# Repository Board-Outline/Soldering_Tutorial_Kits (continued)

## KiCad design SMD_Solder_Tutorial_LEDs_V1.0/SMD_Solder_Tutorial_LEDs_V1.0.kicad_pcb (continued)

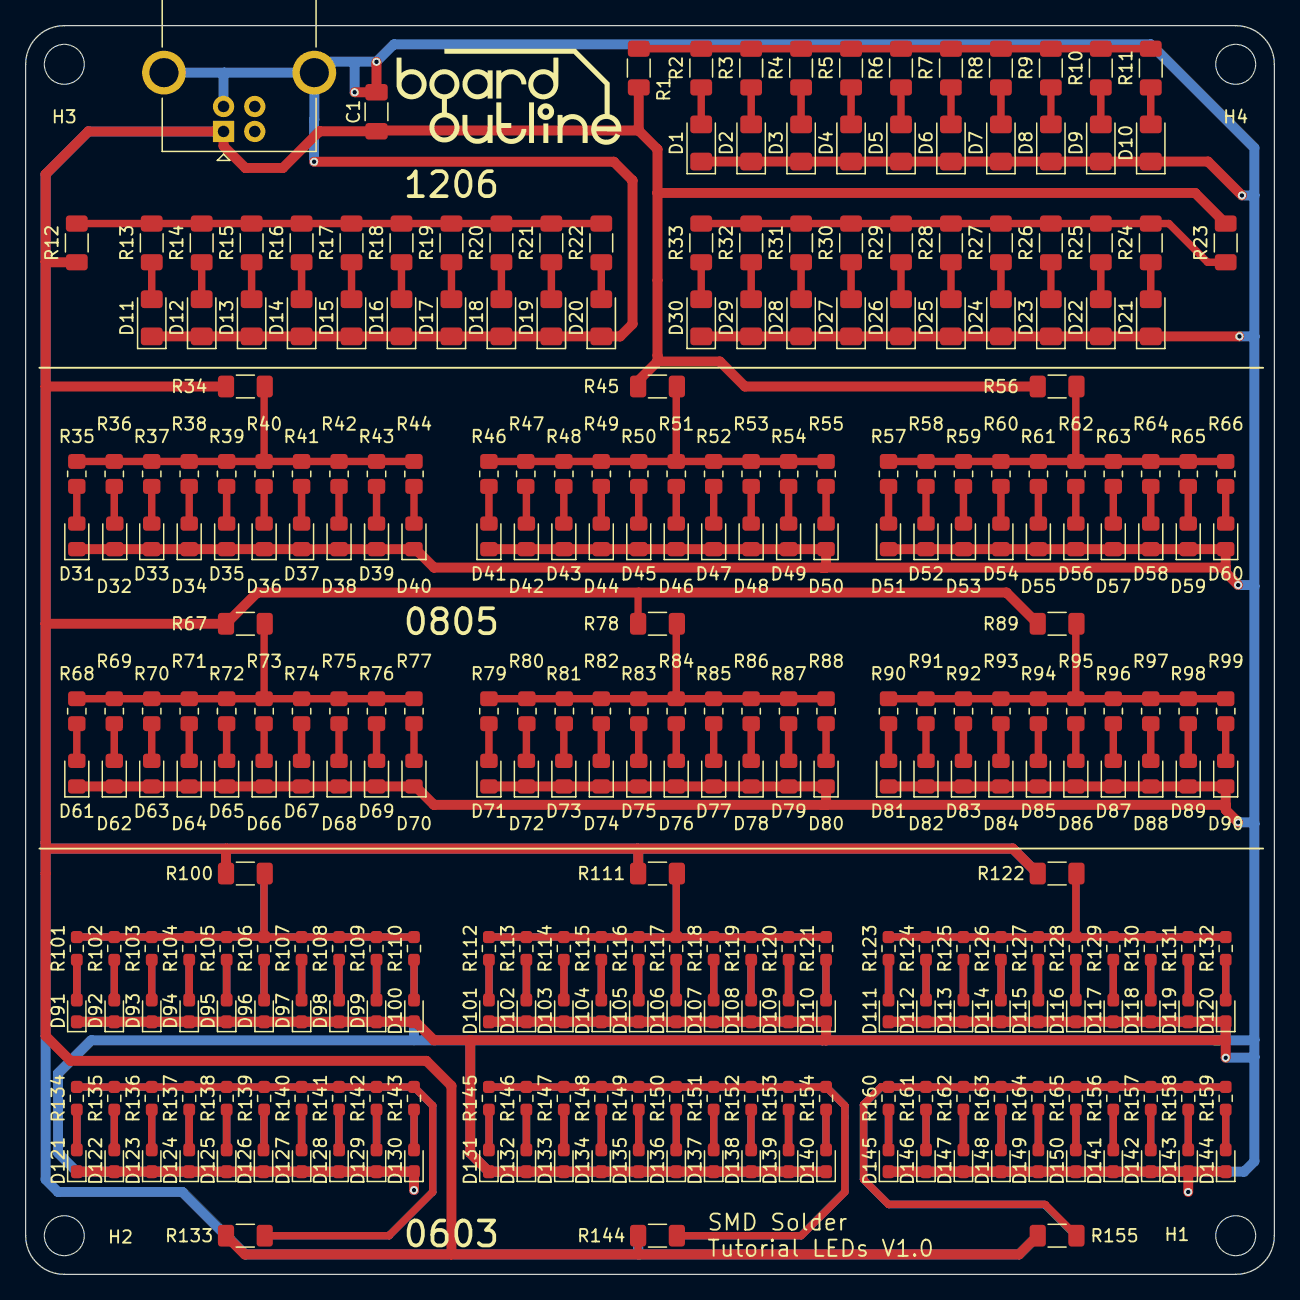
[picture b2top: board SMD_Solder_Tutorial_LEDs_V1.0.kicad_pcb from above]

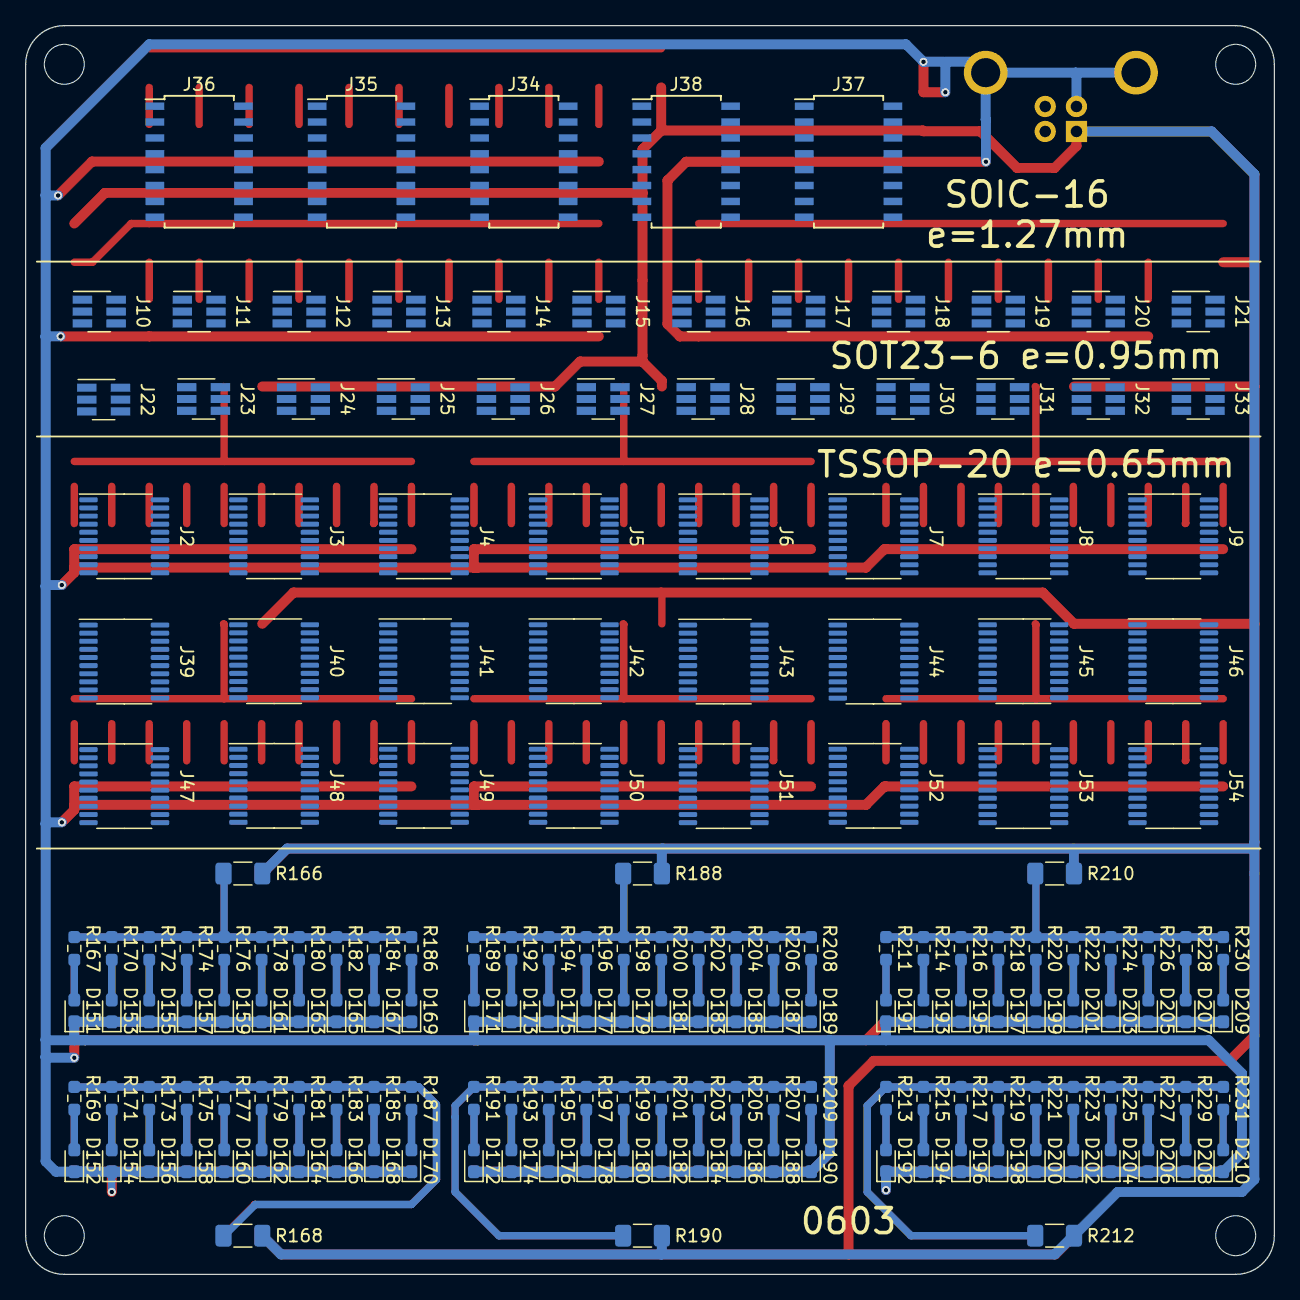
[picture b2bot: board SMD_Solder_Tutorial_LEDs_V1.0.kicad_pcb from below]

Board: 2 copper layers, 100.0 x 100.0 mm, 500 parts (179 on the bottom side), 233 nets.

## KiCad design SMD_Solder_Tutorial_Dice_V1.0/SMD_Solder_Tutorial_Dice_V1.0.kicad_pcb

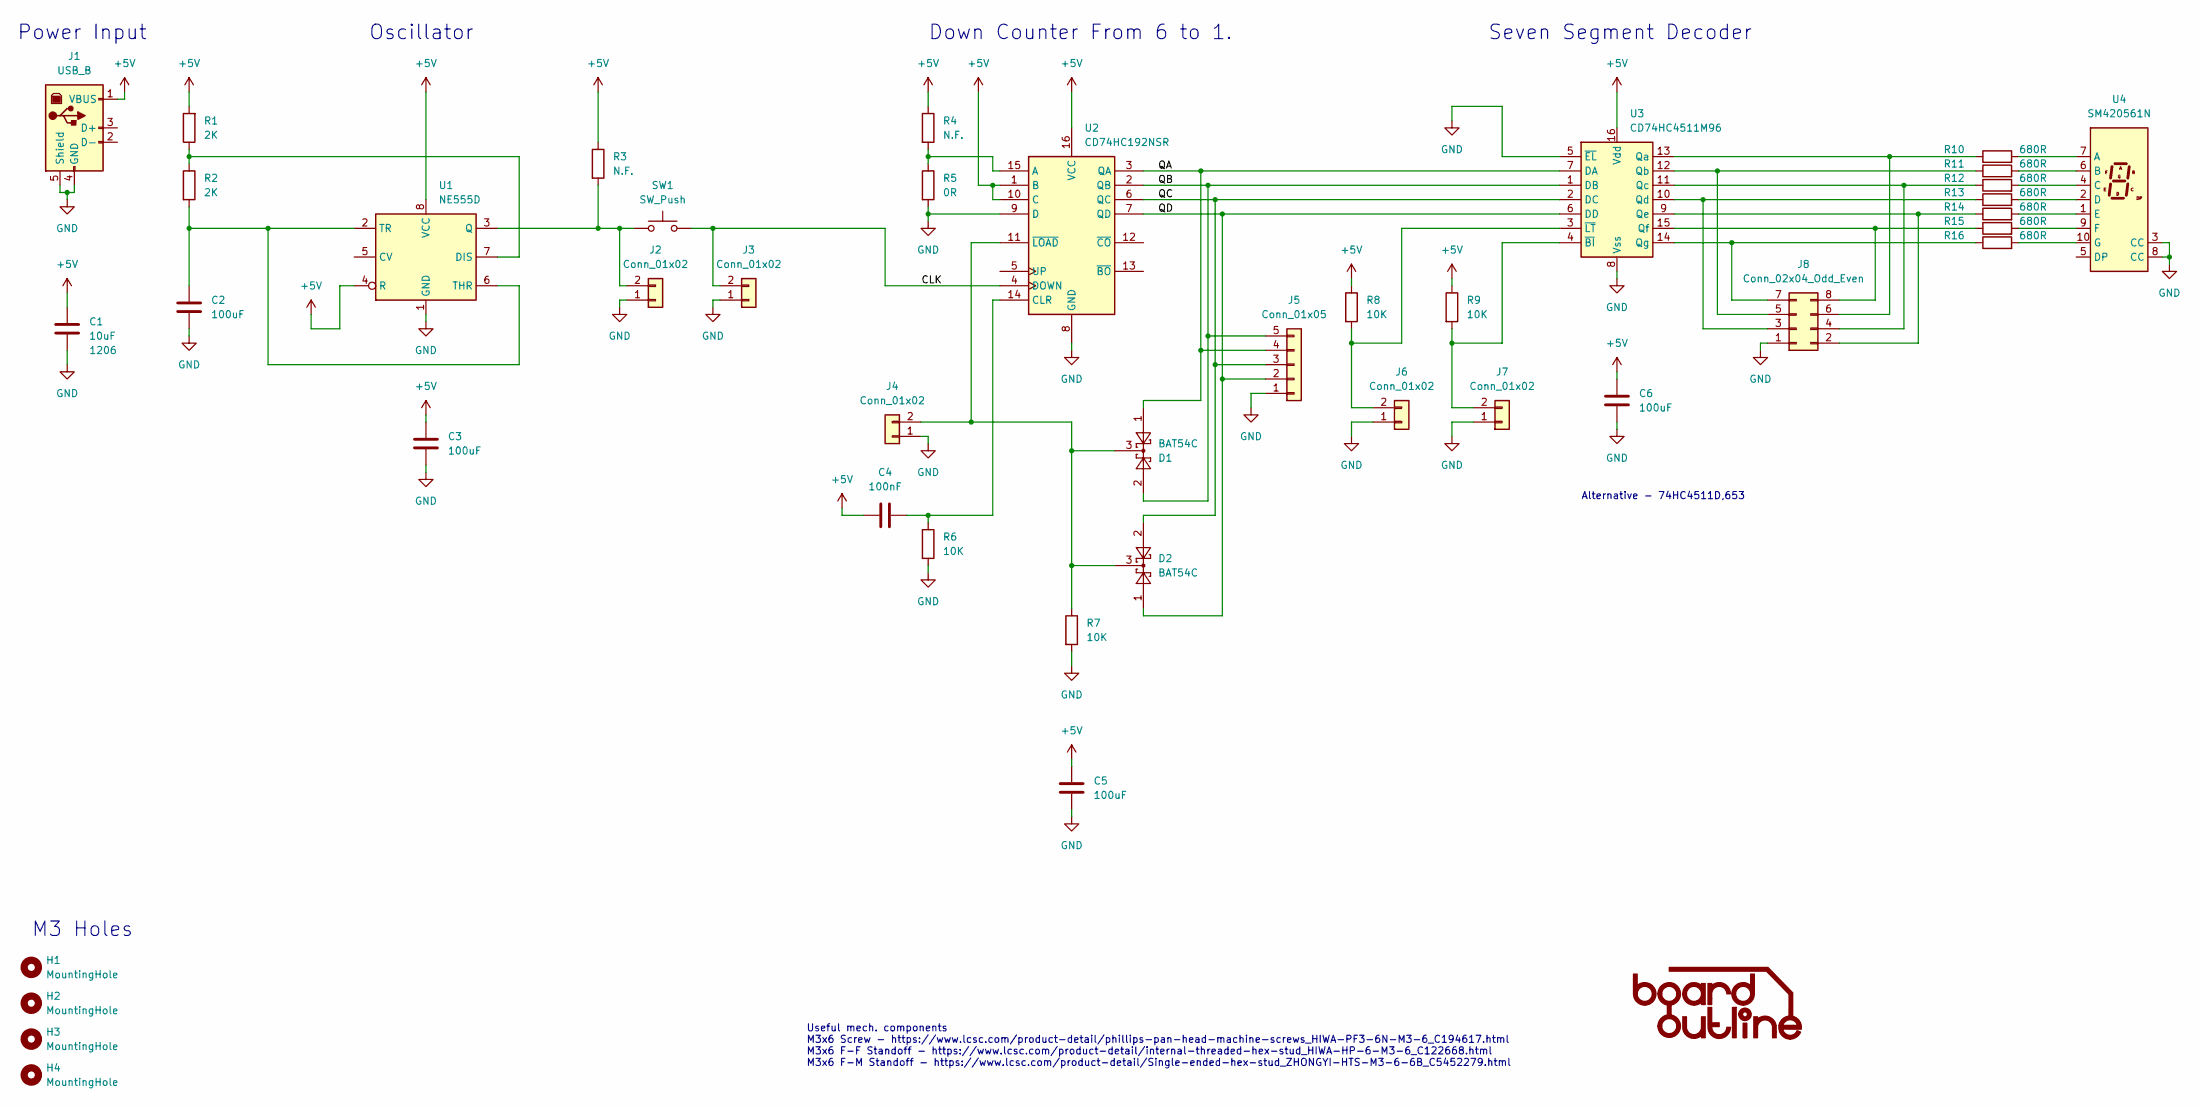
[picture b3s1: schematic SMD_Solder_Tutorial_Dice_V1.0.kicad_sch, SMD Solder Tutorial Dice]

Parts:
C1: 10uF; C_1206_3216Metric_Pad1.33x1.80mm_HandSolder
C2, C3, C5, C6: 100uF; C_0805_2012Metric_Pad1.18x1.45mm_HandSolder
C4: 100nF; C_0805_2012Metric_Pad1.18x1.45mm_HandSolder
D1, D2: BAT54C; SOT-23
H1, H2, H3, H4: MountingHole; MountingHole_3.2mm_M3_DIN965
J1: USB_B; USB_B_OST_USB-B1HSxx_Horizontal; Manufacturer Part Number USB-B10-BRW
J2, J3, J4, J6, J7: Conn_01x02; PinHeader_1x02_P2.54mm_Vertical
J5: Conn_01x05; PinHeader_1x05_P2.54mm_Vertical
J8: Conn_02x04_Odd_Even; PinHeader_2x04_P2.54mm_Vertical
R1, R2: 2K; R_0805_2012Metric_Pad1.20x1.40mm_HandSolder
R3, R4: N.F.; R_0805_2012Metric_Pad1.20x1.40mm_HandSolder
R5: 0R; R_0805_2012Metric_Pad1.20x1.40mm_HandSolder
R6, R7, R8, R9: 10K; R_0805_2012Metric_Pad1.20x1.40mm_HandSolder
R10, R11, R12, R13, R14, R15, R16: 680R; R_0805_2012Metric_Pad1.20x1.40mm_HandSolder
SW1: SW_Push; SW_PUSH_6mm; Manufacturer Part Number TSD001A05526A03
U1: NE555D; SOIC-8_3.9x4.9mm_P1.27mm; Manufacturer Part Number NE555DR-JSM
U2: CD74HC192NSR; SOIC-16W_5.3x10.2mm_P1.27mm; Manufacturer Part Number SN74HC192DR(LX)
U3: CD74HC4511M96; SOIC-16W_5.3x10.2mm_P1.27mm; Manufacturer Part Number CD74HC4511M96
U4: SM420561N; 7SegmentLED_LTS6760_LTS6780; Manufacturer Part Number SM420561N

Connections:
+5V: C1.1, C3.1, C4.1, C5.1, C6.1, J1.1 (VBUS), R1.2, R3.1, R4.1, R8.1, R9.1, U1.4 (R), U1.8 (VCC), U2.1 (B), U2.10 (C), U2.16 (VCC), U3.16 (Vdd)
/CLK: J3.2, SW1.2, U2.4 (DOWN)
/QA: D1.1, J5.4, U2.3 (QA), U3.7 (DA)
/QB: D1.2, J5.5, U2.2 (QB), U3.1 (DB)
/QC: D2.2, J5.3, U2.6 (QC), U3.2 (DC)
/QD: D2.1, J5.2, U2.7 (QD), U3.6 (DD)
GND: C1.2, C2.2, C3.2, C5.2, C6.2, J1.4 (GND), J1.5 (Shield), J2.1, J3.1, J4.1, J5.1, J6.1, J7.1, J8.1, R5.2, R6.2, R7.2, U1.1 (GND), U2.8 (GND), U2.9 (D), U3.5 (~EL), U3.8 (Vss), U4.3 (CC), U4.8 (CC)
unnamed: J2.2, R3.2, SW1.1, U1.3 (Q)
unnamed: D1.3, D2.3, J4.2, R7.1, U2.11 (~LOAD)
unnamed: J6.2, R8.2, U3.3 (~LT)
unnamed: J7.2, R9.2, U3.4 (~BI)
unnamed: J8.2, R14.1, U3.9 (Qe)
unnamed: J8.3, R13.1, U3.10 (Qd)
unnamed: J8.4, R12.1, U3.11 (Qc)
unnamed: J8.5, R11.1, U3.12 (Qb)
unnamed: J8.6, R10.1, U3.13 (Qa)
unnamed: J8.7, R16.1, U3.14 (Qg)
unnamed: J8.8, R15.1, U3.15 (Qf)
unnamed: R1.1, R2.1, U1.7 (DIS)
unnamed: C2.1, R2.2, U1.2 (TR), U1.6 (THR)
unnamed: R4.2, R5.1, U2.15 (A)
unnamed: C4.2, R6.1, U2.14 (CLR)
unnamed: R10.2, U4.7 (A)
unnamed: R11.2, U4.6 (B)
unnamed: R12.2, U4.4 (C)
unnamed: R13.2, U4.2 (D)
unnamed: R14.2, U4.1 (E)
unnamed: R15.2, U4.9 (F)
unnamed: R16.2, U4.10 (G)

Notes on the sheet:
Power Input
Useful mech. components M3x6 Screw - https://www.lcsc.com/product-detail/phillips-pan-head-machine-screws_HIWA-PF3-6N-M3-6_C194617.html M3x6 F-F Standoff - https://www.lcsc.com/product-detail/internal-threaded-hex-stud_HIWA-HP-6-M3-6_C122668.html M3x6 F-M Standoff - https://www.lcsc.com/product-det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
Alternative - 74HC4511D,653
M3 Holes
Seven Segment Decoder
Oscillator
Down Counter From 6 to 1.

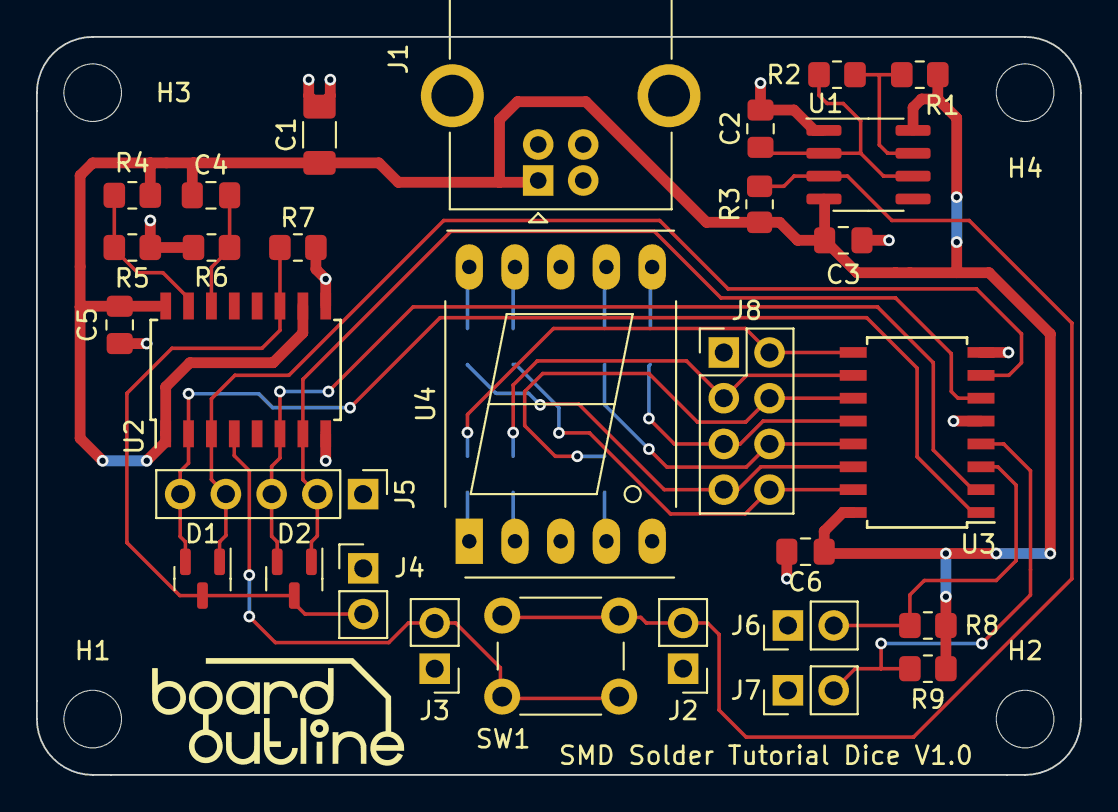
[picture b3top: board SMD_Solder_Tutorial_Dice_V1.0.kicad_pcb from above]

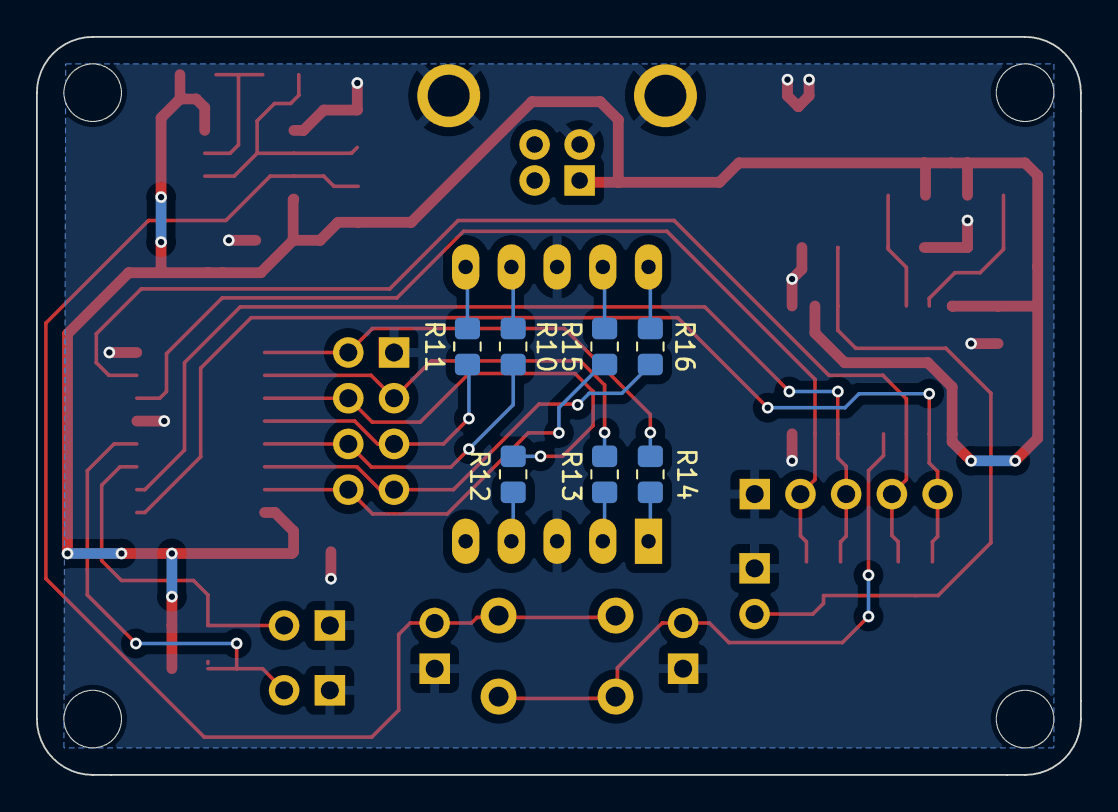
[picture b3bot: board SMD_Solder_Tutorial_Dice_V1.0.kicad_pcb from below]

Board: 2 copper layers, 58.0 x 41.0 mm, 41 parts (7 on the bottom side), 29 nets.

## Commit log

2024-05-25 Update to README and added license policy
